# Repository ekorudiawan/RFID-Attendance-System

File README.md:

# RFID-Attendance-System
RFID Attendance System

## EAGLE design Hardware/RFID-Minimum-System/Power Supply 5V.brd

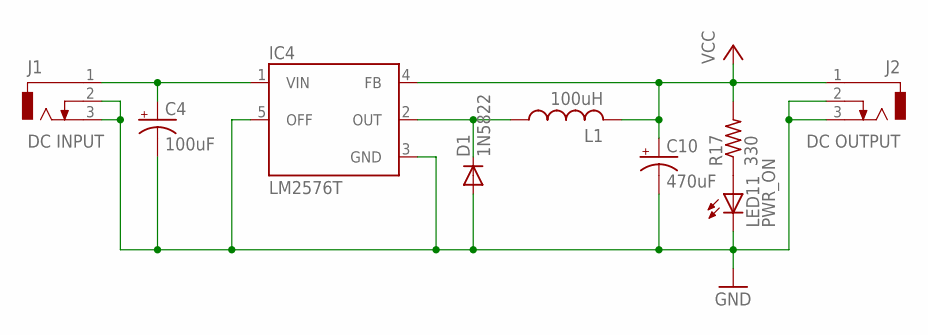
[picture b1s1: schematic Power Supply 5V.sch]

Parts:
C4: 100uF; E2,5-6
C10: 470uF; E3,5-8
D1: 1N5822; DO201-15
IC4: LM2576T; TO220-5
J1: DC INPUT; DCJ0202
J2: DC OUTPUT; DCJ0202
L1: 100uH; TJ3-U2
LED11: PWR_ON; LED3MM
R17: 330; 0207/10

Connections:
GND: C4.-, C10.-, D1.A, IC4.3 (GND), IC4.5 (OFF), J1.2, J1.3, J2.2, J2.3, LED11.K (C)
unnamed: C4.+, IC4.1 (VIN), J1.1
unnamed: D1.C, IC4.2 (OUT), L1.1
unnamed: LED11.A, R17.1
VCC: C10.+, IC4.4 (FB), J2.1, L1.2, R17.2

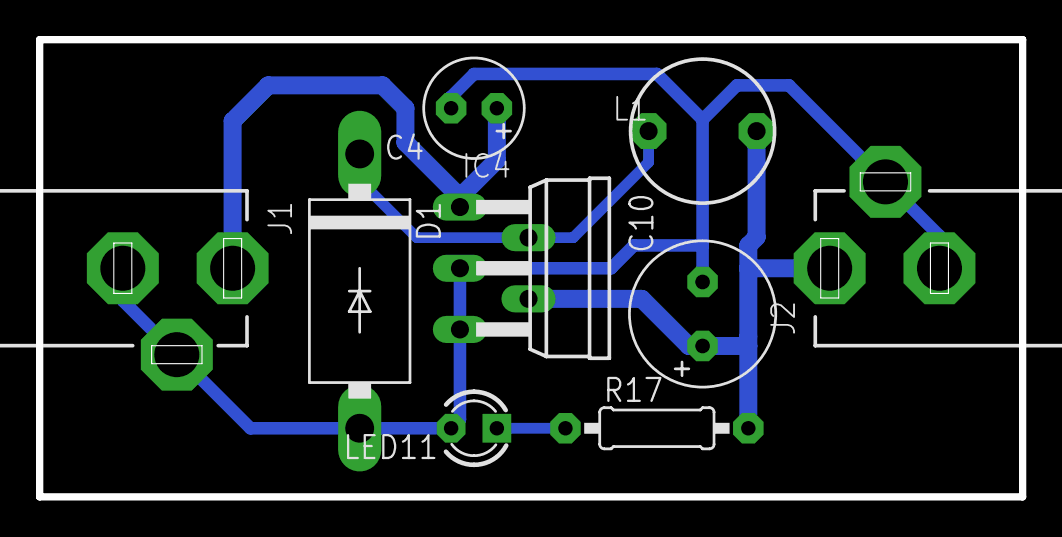
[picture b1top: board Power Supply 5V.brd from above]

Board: 2 copper layers, 54.6 x 25.4 mm, 9 parts (0 on the bottom side), 5 nets.

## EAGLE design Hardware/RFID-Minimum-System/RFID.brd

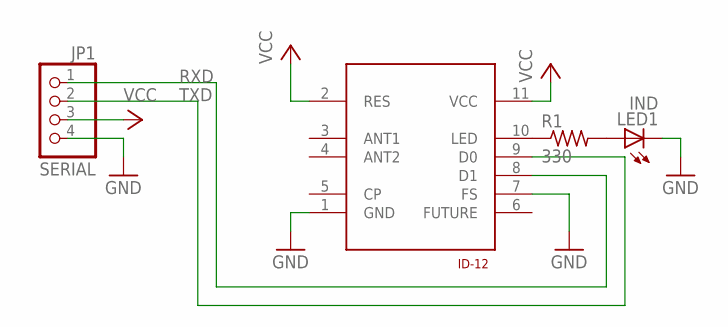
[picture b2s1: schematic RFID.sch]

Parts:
JP1: SERIAL; 1X04
LED1: IND; LED3MM
R1: 330; 0207/10
U$1: ID-20

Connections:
GND: JP1.4, LED1.K (C), U$1.1 (GND), U$1.7 (FS)
unnamed: R1.1, U$1.10 (LED)
unnamed: LED1.A, R1.2
RXD: JP1.1, U$1.8 (D1)
TXD: JP1.2, U$1.9 (D0)
VCC: JP1.3, U$1.2 (RES), U$1.11 (VCC)

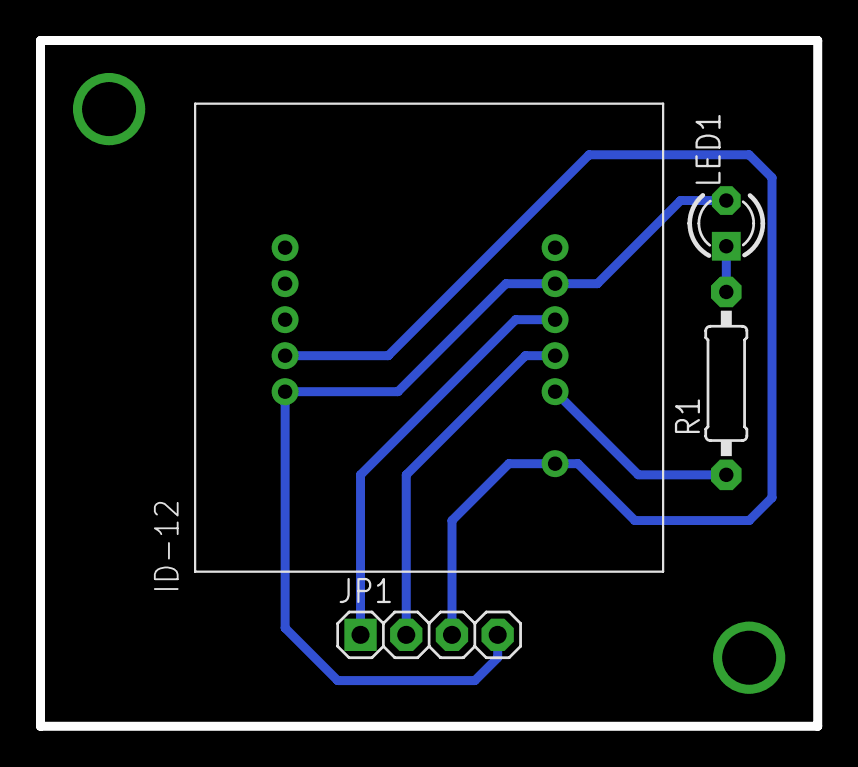
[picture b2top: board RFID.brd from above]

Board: 2 copper layers, 43.2 x 38.1 mm, 4 parts (0 on the bottom side), 6 nets.

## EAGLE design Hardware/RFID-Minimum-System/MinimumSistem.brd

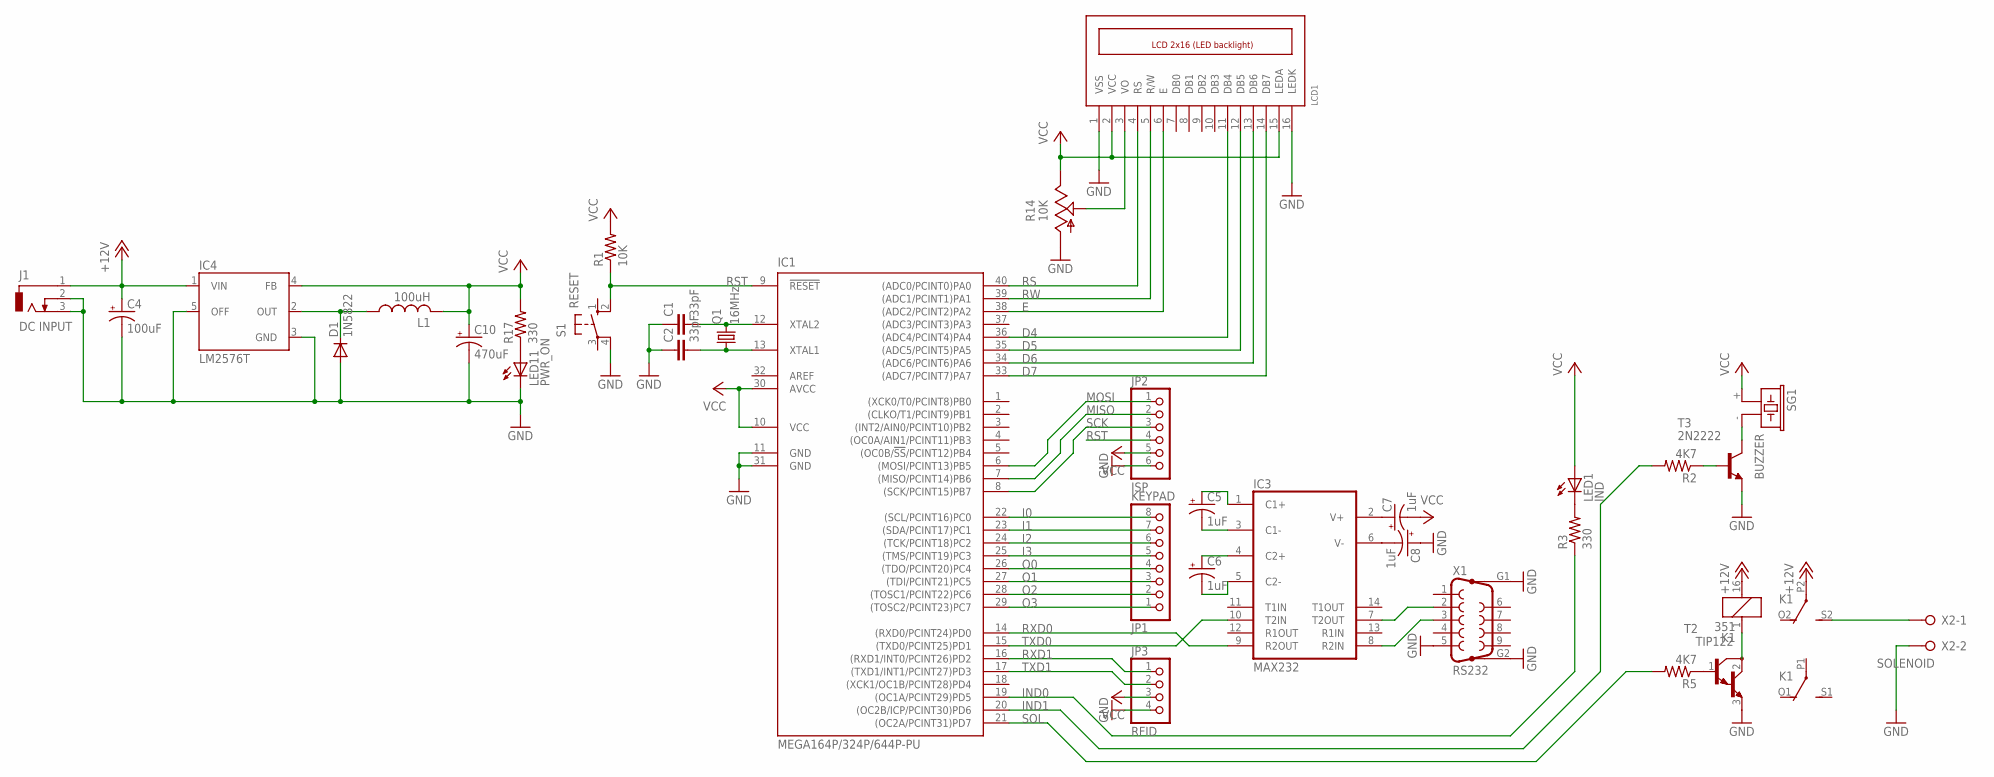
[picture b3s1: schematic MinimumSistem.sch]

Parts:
C1, C2: 33pF; C025-024X044
C4: 100uF; E2,5-6
C5, C6, C7, C8: 1uF; E2-4
C10: 470uF; E3,5-8
D1: 1N5822; DO201-15
IC1: MEGA164P/324P/644P-PU; DIL40
IC3: MAX232; DIL16
IC4: LM2576T; TO220-5
J1: DC INPUT; DCJ0202
JP1: KEYPAD; 1X08/90
JP2: ISP; 1X06
JP3: RFID; 1X04
K1: 351
L1: 100uH; TJ3-U2
LCD1: LCD_2X16; HY-1602F
LED1: IND; LED5MM
LED11: PWR_ON; LED3MM
Q1: 16MHz; HC49/S
R1: 10K; 0207/10
R2, R5: 4K7; 0207/10
R3, R17: 330; 0207/10
R14: 10K; CA6V
S1: RESET; B3F-10XX
SG1: BUZZER; F/CM12P
T2: TIP122; TO220
T3: 2N2222; TO92-EBC-OVAL
X1: RS232; F09HP
X2: SOLENOID; W237-132

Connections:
+12V: C4.+, IC4.1 (VIN), J1.1, K1.16 (2), K1.P2
AREF: IC1.32 (AREF)
D4: IC1.36 ((ADC4/PCINT4)PA4), LCD1.11 (DB4)
D5: IC1.35 ((ADC5/PCINT5)PA5), LCD1.12 (DB5)
D6: IC1.34 ((ADC6/PCINT6)PA6), LCD1.13 (DB6)
D7: IC1.33 ((ADC7/PCINT7)PA7), LCD1.14 (DB7)
E: IC1.38 ((ADC2/PCINT2)PA2), LCD1.6 (E)
GND: C1.1, C2.1, C4.-, C8.+, C10.-, D1.A, IC1.11 (GND), IC1.31 (GND), IC3.15 (GND), IC4.3 (GND), IC4.5 (OFF), J1.2, J1.3, JP2.6, JP3.4, LCD1.1 (VSS), LCD1.16 (LEDK), LED11.K (C), R14.A, S1.4 (P1), T2.3 (E), T3.E, X1.5, X1.G1, X1.G2, X2.2
I0: IC1.22 ((SCL/PCINT16)PC0), JP1.8
I1: IC1.23 ((SDA/PCINT17)PC1), JP1.7
I2: IC1.24 ((TCK/PCINT18)PC2), JP1.6
I3: IC1.25 ((TMS/PCINT19)PC3), JP1.5
IND0: IC1.19 ((OC1A/PCINT29)PD5), R3.1
IND1: IC1.20 ((OC2B/ICP/PCINT30)PD6), R2.2
MISO: IC1.7 ((MISO/PCINT14)PB6), JP2.2
MOSI: IC1.6 ((MOSI/PCINT13)PB5), JP2.1
unnamed: C1.2, IC1.12 (XTAL2), Q1.2
unnamed: C2.2, IC1.13 (XTAL1), Q1.1
unnamed: R5.1, T2.1 (B)
unnamed: K1.1, T2.2 (C)
unnamed: LED1.K (C), R3.2
unnamed: K1.S2 (S), X2.1
unnamed: R2.1, T3.B
unnamed: SG1.- (2), T3.C
unnamed: C5.-, IC3.3 (C1-)
unnamed: C6.+, IC3.4 (C2+)
unnamed: C5.+, IC3.1 (C1+)
unnamed: C6.-, IC3.5 (C2-)
unnamed: C7.+, IC3.2 (V+)
unnamed: C8.-, IC3.6 (V-)
unnamed: IC3.7 (T2OUT), X1.2
unnamed: IC3.8 (R2IN), X1.3
unnamed: LCD1.3 (VO), R14.S
unnamed: D1.C, IC4.2 (OUT), L1.1
unnamed: LED11.A, R17.1
O0: IC1.26 ((TDO/PCINT20)PC4), JP1.4
O1: IC1.27 ((TDI/PCINT21)PC5), JP1.3
O2: IC1.28 ((TOSC1/PCINT22)PC6), JP1.2
O3: IC1.29 ((TOSC2/PCINT23)PC7), JP1.1
RS: IC1.40 ((ADC0/PCINT0)PA0), LCD1.4 (RS)
RST: IC1.9 (!RESET), JP2.4, R1.1, S1.2 (S1)
RW: IC1.39 ((ADC1/PCINT1)PA1), LCD1.5 (R/W)
RXD0: IC1.14 ((RXD0/PCINT24)PD0), IC3.9 (R2OUT)
RXD1: IC1.16 ((RXD1/INT0/PCINT26)PD2), JP3.1
SCK: IC1.8 ((SCK/PCINT15)PB7), JP2.3
SOL: IC1.21 ((OC2A/PCINT31)PD7), R5.2
TXD0: IC1.15 ((TXD0/PCINT25)PD1), IC3.10 (T2IN)
TXD1: IC1.17 ((TXD1/INT1/PCINT27)PD3), JP3.2
VCC: C7.-, C10.+, IC1.10 (VCC), IC1.30 (AVCC), IC3.16 (VCC), IC4.4 (FB), JP2.5, JP3.3, L1.2, LCD1.2 (VCC), LCD1.15 (LEDA), LED1.A, R1.2, R14.E, R17.2, SG1.+ (1)

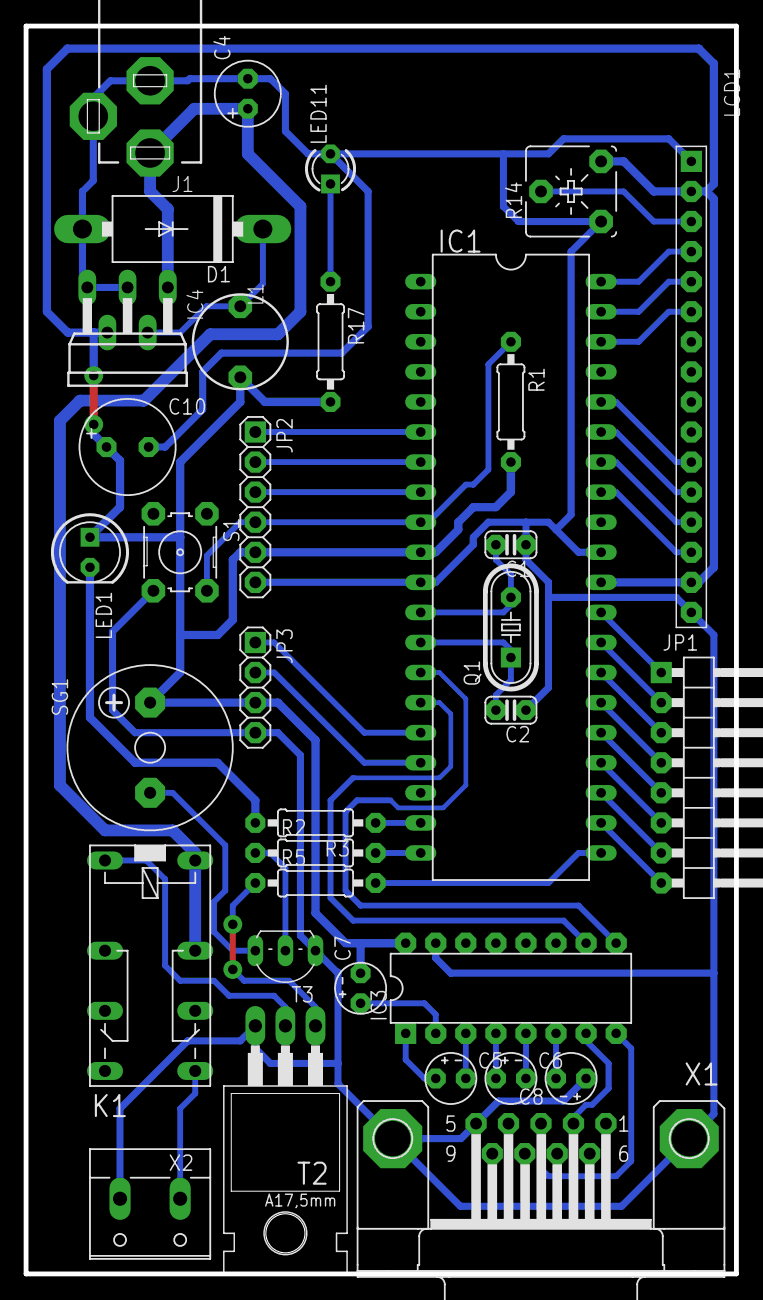
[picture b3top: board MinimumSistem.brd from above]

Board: 2 copper layers, 60.0 x 105.4 mm, 34 parts (0 on the bottom side), 48 nets.

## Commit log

2017-10-03 Added HW & SW Files
2017-10-03 Added doc files
